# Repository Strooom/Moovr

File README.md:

# Welcome to Moovr
a CNC Controller project

please read all about it in the Wiki : https://github.com/Strooom/Moovr/wiki

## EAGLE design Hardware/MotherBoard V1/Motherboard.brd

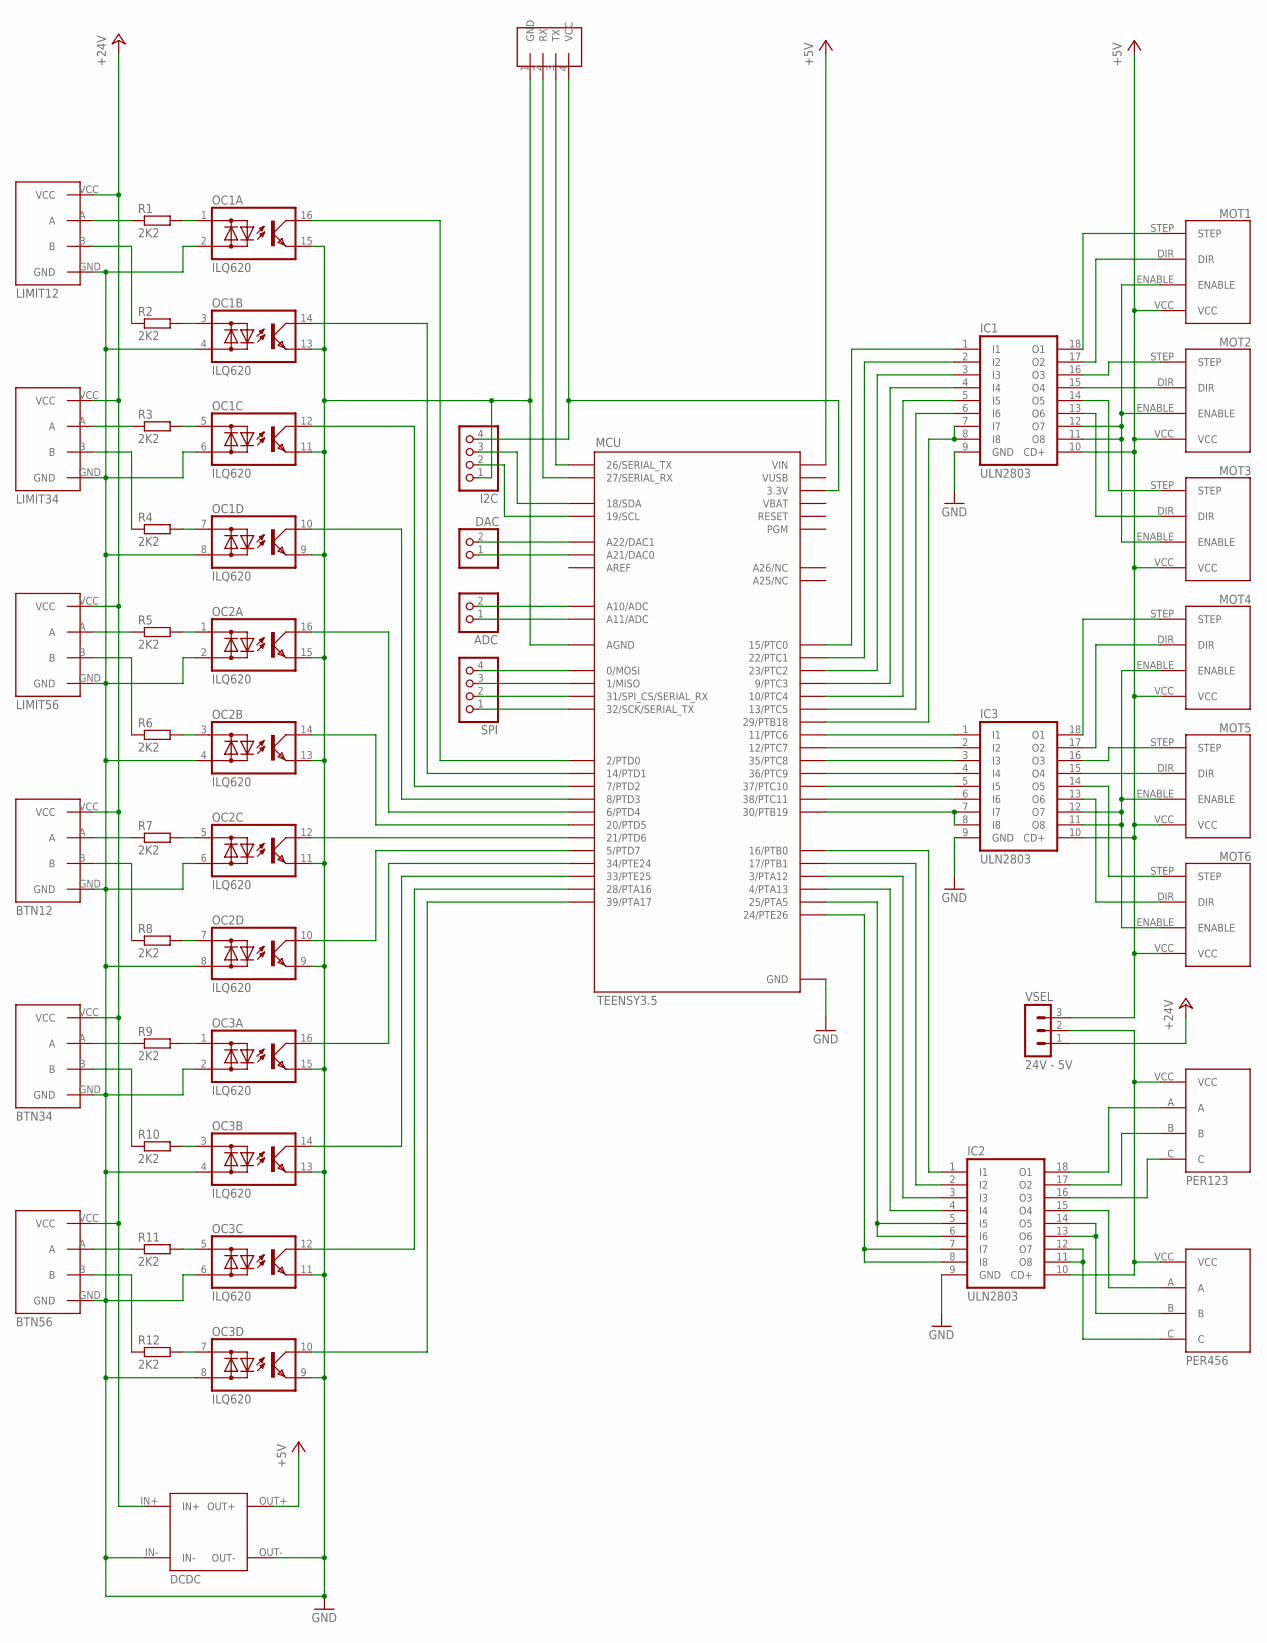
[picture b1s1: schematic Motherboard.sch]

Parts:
ADC: PINHD-1X2; 1X02
BTN12, BTN34, BTN56: CONN4B
DAC: PINHD-1X2; 1X02
DCDC: DCDC
I2C: PINHD-1X4; 1X04
IC1, IC2, IC3: ULN2803; DIL18
LIMIT12, LIMIT34, LIMIT56: CONN4B
MCU: TEENSY3.5; TEENSY_3.5_ALL_PINS
MOT1, MOT2, MOT3, MOT4, MOT5, MOT6: CONN4
OC1, OC2, OC3: ILQ620; DIL16
PER123, PER456: CONN4C
R1, R2, R3, R4, R5, R6, R7, R8, R9, R10, R11, R12: 2K2; 0207/10
SPI: PINHD-1X4; 1X04
U$1: SERIAL-SUBD9-IF
VSEL: 24V - 5V; MA03-1

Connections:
3.3V: I2C.4, MCU.3.3V, MCU.3.3V3 (3.3V), MCU.3.3V4 (3.3V), U$1.4 (VCC)
+5V: DCDC.OUT+, IC1.10 (CD+), IC3.10 (CD+), MCU.VIN, MOT1.VCC, MOT2.VCC, MOT3.VCC, MOT4.VCC, MOT5.VCC, MOT6.VCC, VSEL.3
+24V: BTN12.VCC, BTN34.VCC, BTN56.VCC, DCDC.IN+, LIMIT12.VCC, LIMIT34.VCC, LIMIT56.VCC, VSEL.1
+PER: IC2.10 (CD+), PER123.VCC, PER456.VCC, VSEL.2
AREF: MCU.AREF
BT12A: BTN12.A, R7.1
BT12AR: OC2.5 (AC1), R7.2
BT12B: BTN12.B, R8.1
BT12BR: OC2.7 (AC1), R8.2
BT34A: BTN34.A, R9.1
BT34AR: OC3.1 (AC1), R9.2
BT34B: BTN34.B, R10.1
BT34BR: OC3.3 (AC1), R10.2
BT56A: BTN56.A, R11.1
BT56AR: OC3.5 (AC1), R11.2
BT56B: BTN56.B, R12.1
BT56BR: OC3.7 (AC1), R12.2
GND: BTN12.GND, BTN34.GND, BTN56.GND, DCDC.IN-, DCDC.OUT-, I2C.1, IC1.9 (GND), IC2.9 (GND), IC3.9 (GND), LIMIT12.GND, LIMIT34.GND, LIMIT56.GND, MCU.AGND, MCU.GND, MCU.GND1 (GND), MCU.GND3 (GND), MCU.GND4 (GND), MCU.GND6 (GND), OC1.2 (AC2), OC1.4 (AC2), OC1.6 (AC2), OC1.8 (AC2), OC1.9 (E), OC1.11 (E), OC1.13 (E), OC1.15 (E), OC2.2 (AC2), OC2.4 (AC2), OC2.6 (AC2), OC2.8 (AC2), OC2.9 (E), OC2.11 (E), OC2.13 (E), OC2.15 (E), OC3.2 (AC2), OC3.4 (AC2), OC3.6 (AC2), OC3.8 (AC2), OC3.9 (E), OC3.11 (E), OC3.13 (E), OC3.15 (E), U$1.1 (GND)
L12A: LIMIT12.A, R1.1
L12AR: OC1.1 (AC1), R1.2
L12B: LIMIT12.B, R2.1
L12BR: OC1.3 (AC1), R2.2
L34A: LIMIT34.A, R3.1
L34AR: OC1.5 (AC1), R3.2
L34B: LIMIT34.B, R4.1
L34BR: OC1.7 (AC1), R4.2
L56A: LIMIT56.A, R5.1
L56AR: OC2.1 (AC1), R5.2
L56B: LIMIT56.B, R6.1
L56BR: OC2.3 (AC1), R6.2
LDIR1: IC1.2 (I2), MCU.22/A8 (22/PTC1)
LDIR2: IC1.4 (I4), MCU.9 (9/PTC3)
LDIR3: IC1.6 (I6), MCU.13 (13/PTC5)
LDIR4: IC3.2 (I2), MCU.12 (12/PTC7)
LDIR5: IC3.4 (I4), MCU.36/A17 (36/PTC9)
LDIR6: IC3.6 (I6), MCU.38/A19 (38/PTC11)
LENABLE123: IC1.7 (I7), IC1.8 (I8), MCU.29 (29/PTB18)
LENABLE456: IC3.7 (I7), IC3.8 (I8), MCU.30 (30/PTB19)
LIN01: MCU.2 (2/PTD0), OC1.16 (C)
LIN02: MCU.14/A0 (14/PTD1), OC1.14 (C)
LIN03: MCU.7 (7/PTD2), OC1.12 (C)
LIN04: MCU.8 (8/PTD3), OC1.10 (C)
LIN05: MCU.6 (6/PTD4), OC2.16 (C)
LIN06: MCU.20/A6 (20/PTD5), OC2.14 (C)
LIN07: MCU.21/A7 (21/PTD6), OC2.12 (C)
LIN08: MCU.5 (5/PTD7), OC2.10 (C)
LIN09: MCU.34/A15 (34/PTE24), OC3.16 (C)
LIN10: MCU.33/A14 (33/PTE25), OC3.14 (C)
LIN11: MCU.28 (28/PTA16), OC3.12 (C)
LIN12: MCU.39/A20 (39/PTA17), OC3.10 (C)
LPER1A: IC2.1 (I1), MCU.16/A2 (16/PTB0)
LPER1B: IC2.2 (I2), MCU.17/A3 (17/PTB1)
LPER1C: IC2.3 (I3), MCU.3 (3/PTA12)
LPER2A: IC2.4 (I4), MCU.4 (4/PTA13)
LPER2B: IC2.5 (I5), IC2.6 (I6), MCU.25 (25/PTA5)
LPER2C: IC2.7 (I7), IC2.8 (I8), MCU.24 (24/PTE26)
LSTEP1: IC1.1 (I1), MCU.15/A1 (15/PTC0)
LSTEP2: IC1.3 (I3), MCU.23/A9 (23/PTC2)
LSTEP3: IC1.5 (I5), MCU.10 (10/PTC4)
LSTEP4: IC3.1 (I1), MCU.11 (11/PTC6)
LSTEP5: IC3.3 (I3), MCU.35/A16 (35/PTC8)
LSTEP6: IC3.5 (I5), MCU.37/A18 (37/PTC10)
M1DIR: IC1.17 (O2), MOT1.DIR
M1STEP: IC1.18 (O1), MOT1.STEP
M2DIR: IC1.15 (O4), MOT2.DIR
M2STEP: IC1.16 (O3), MOT2.STEP
M3DIR: IC1.13 (O6), MOT3.DIR
M3STEP: IC1.14 (O5), MOT3.STEP
M4DIR: IC3.17 (O2), MOT4.DIR
M4STEP: IC3.18 (O1), MOT4.STEP
M5DIR: IC3.15 (O4), MOT5.DIR
M5STEP: IC3.16 (O3), MOT5.STEP
M6DIR: IC3.13 (O6), MOT6.DIR
M6STEP: IC3.14 (O5), MOT6.STEP
M123ENABLE: IC1.11 (O8), IC1.12 (O7), MOT1.ENABLE, MOT2.ENABLE, MOT3.ENABLE
M456ENABLE: IC3.11 (O8), IC3.12 (O7), MOT4.ENABLE, MOT5.ENABLE, MOT6.ENABLE
unnamed: I2C.3, MCU.18/A4 (18/SDA)
unnamed: I2C.2, MCU.19/A5 (19/SCL)
unnamed: DAC.2, MCU.A22 (A22/DAC1)
unnamed: DAC.1, MCU.A21 (A21/DAC0)
unnamed: ADC.2, MCU.A10 (A10/ADC)
unnamed: ADC.1, MCU.A11 (A11/ADC)
unnamed: MCU.0 (0/MOSI), SPI.4
unnamed: MCU.1 (1/MISO), SPI.3
unnamed: MCU.31/A12 (31/SPI_CS/SERIAL_RX), SPI.2
unnamed: MCU.32/A13 (32/SCK/SERIAL_TX), SPI.1
PER123A: IC2.18 (O1), PER123.A
PER123B: IC2.17 (O2), PER123.B
PER123C: IC2.16 (O3), PER123.C
PER456A: IC2.15 (O4), PER456.A
PER456B: IC2.13 (O6), IC2.14 (O5), PER456.B
PER456C: IC2.11 (O8), IC2.12 (O7), PER456.C
SERIALRX: MCU.27 (27/SERIAL_RX), U$1.2 (RX)
SERIALTX: MCU.26 (26/SERIAL_TX), U$1.3 (TX)
VBAT: MCU.VBAT
VUSB: MCU.VUSB

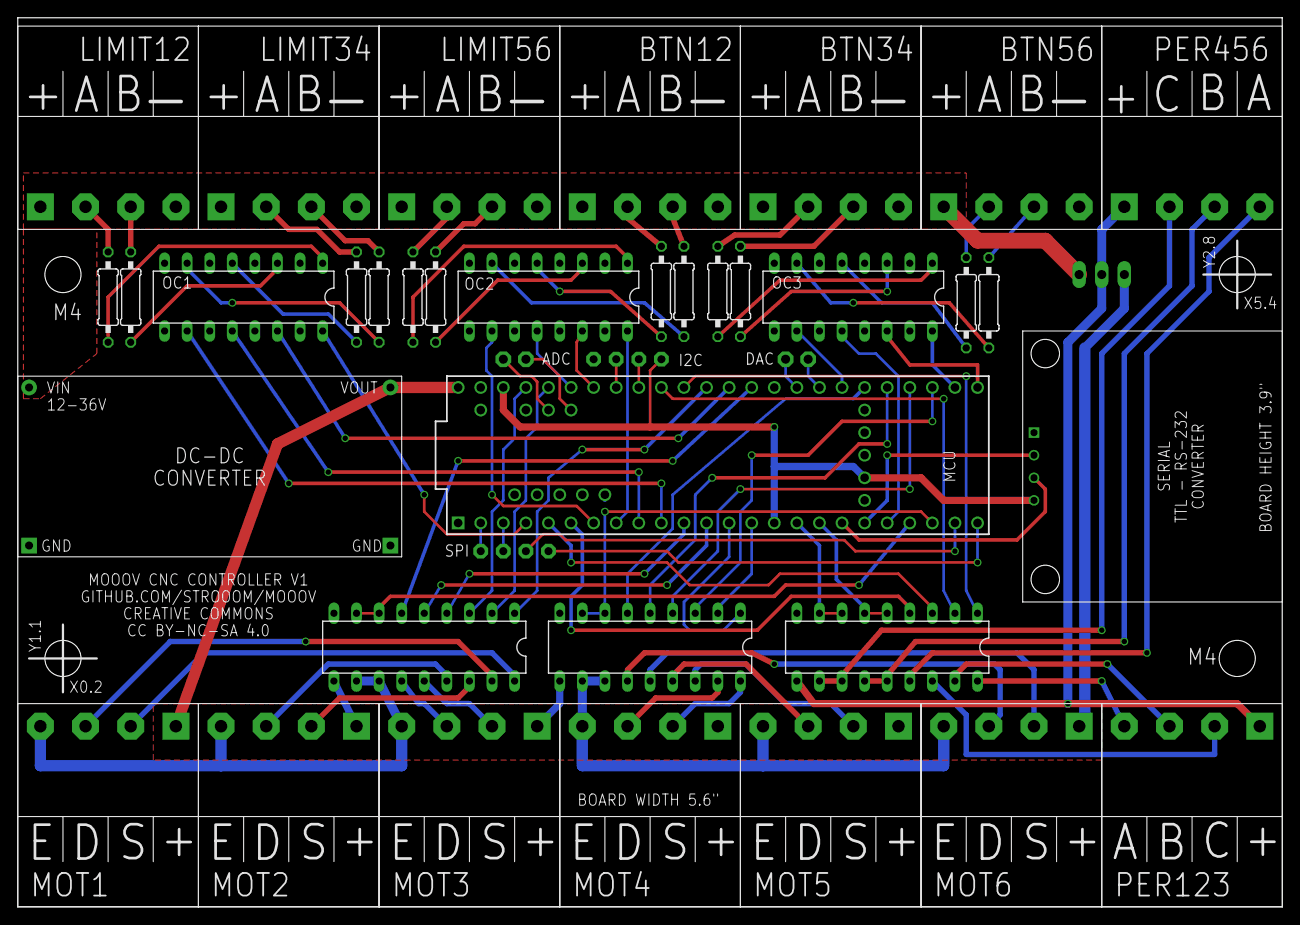
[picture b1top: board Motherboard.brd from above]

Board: 2 copper layers, 142.2 x 100.0 mm, 40 parts (0 on the bottom side), 93 nets.

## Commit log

2017-01-04 Kickoff
    Commit Zero
2017-01-05 Added CC BY-NC-SA License
2017-01-05 Added Teensy Reference Documents
2017-01-05 Set theme jekyll-theme-cayman
2017-01-10 Adding images for Wiki
2017-01-10 Adding images to documentation
2017-01-10 Added image
2017-01-13 Adding an image
2017-01-19 added sw architecture top-level block diagram
2017-01-20 Added image explaining Circular Buffers
    Terminology and Most needed formula's when accessing the contents in the
    buffers
2017-01-21 Adding some reference materials on the STM32
    Could be a candidate uController
2017-01-21 Stepper Motor Datasheets 23HS22-2804S
2017-01-23 hardware datasheets
    MAX232 / MAX 3232 and STM32F103 datasheet
2017-02-14 Added Reference materials on Teensy 3.2
2017-02-18 Adding EasyDriver datasheets
2017-02-22 Included Teensy GPIO Alternate Functions
2017-02-22 Periodic Interupt Timer documentation
2017-02-23 Added a worksheet with all K64 pins
    So I can make a crosscheck one day..
2017-05-23 Added Schematics and Layout for Motherboard V1
2017-05-27 Semi assembled controller - picture
    Teensy 3.5 on Motherboard, 4 Stepper drivers and one Solid State Relay
2017-06-26 added image of optical limit switch
2019-08-16 First pre-release for code reviewing by community
    This is not a fully working sw release but rather a first publication of
    the code for code review and building up knowledge about the Moovr
    framework.
2020-05-26 commit for code review
2020-12-05 refactoring towards hardware abstraction
2020-12-05 more unit testing
2020-12-05 other updates
2020-12-05 conditional compilation for critical sections
2020-12-05 add machineProperties
2020-12-05 Delete MCU.h
    moved to machineproperties.h
2020-12-05 renames MCU to machineProperties
2020-12-05 renamed stepper to stepbuffer
2020-12-05 adjusted TitelCase to camelCase
2020-12-05 renames
2020-12-05 more consistent naming
2020-12-05 removed old files
2020-12-06 starting getNextStep
2020-12-09 update getNextStep
2020-12-30 refactoring
2021-01-01 cleaner literals
2021-01-03 reordered unitTests
2021-01-12 motionCtrl improvements
2021-01-13 removed duplicate files
2021-01-13 adjusted gitignore
2021-01-13 removing suplicates
2021-01-14 simplifying names
2021-01-14 building the maincontrol stateMachine
2022-05-07 reorganizing folder structure
2022-05-07 ignored VSCodeCounter files
2022-05-25 exclude draw.io backup copies
2022-05-25 add documentation
2022-05-25 add documentation and test plan
2022-05-25 remove testing private members
2022-08-09 reorganised project for Platformio
2022-08-10 reorganised files in folders
2022-08-10 added a 2nd application
    2axis plotter
2022-08-11 reorganised folder structure to simplify dependencies
2022-08-11 improved unit testing of motion
2022-08-12 adding unit tests on motionControl
2022-08-15 reorganizing gcode sourcecode for unit testing
2022-08-16 reorganized old unit test for gCode
2022-08-16 refactored gCode into smaller functions
2022-08-17 motion unit tests
    Fixed some errors in calculation of helical path
2022-08-17 replace uin8_t by faster uint32_t
2022-08-18 fixed issue in motion control unit test
2022-08-18 improving getNextStep()
    add new flowchart and implementation based on that
2022-08-18 improv how sampleTime and motionCtrl work together
2022-08-21 improvements on motionControl
2022-08-23 more unit tests on motionControl
2022-08-24 add 3rd unitTest motionControl
2022-08-24 add unitTest for optimize after feedrate override
2022-08-26 built a first minimal app running on target hw
2022-08-31 first tests on real hardware CNC
2022-09-01 improve G2 G3 angle calculations
2022-09-02 first version of homing
2022-09-03 add unittests for homing
2022-09-04 testing offset after homing
2022-09-04 bug in motionBuffer.flush
2022-09-05 first release with homing - yahoo!
2022-09-08 homing 3 axis
2022-09-08 passes gcode unit tests
2022-09-08 add feedhold during G4
2022-09-08 added lastError to motionBuffer
2022-09-08 renaming for more consistency
2022-09-08 adding minLevel and maxLevel
    for tracking how the bufferlevel behaves in a real application
2022-09-08 add minLevel, maxLevel. Better needsFilling
2022-09-08 first set of unit tests
2022-09-08 cleanup comments
2022-09-17 add modalGroup pathcontrolmode
2022-09-17 interpreting G61 or G64 words
2022-09-17 rename test
2022-09-17 repair tests after renaming class properties
2022-09-18 add unit test for correct number detection
2022-09-18 add more block parsing unit tests
2022-09-23 add unit test as github action
2022-09-25 fixing unit tests as github action
2022-09-25 corrected branch name
2022-09-25 add badge
2022-09-25 updating Todo's

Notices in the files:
Hardware/MotherBoard V1/Motherboard.brd:
CREATIVE COMMONS
CC BY-NC-SA 4.0
